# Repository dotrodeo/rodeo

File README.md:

# Rodeo

A modular **synthesizer hardware ecosystem**: one host *motherboard*, a family of
control-surface *daughterboards*, and *instrument instances* built by combining them.
This repository is the single home for all of it — board designs (KiCad), firmware,
and the design docs that tie them together.

## Layout

The current hardware is **Rev B**, in [`hardware/`](hardware/). Rev A, the prototype
generation that rodeo-001 and rodeo-002 were built on, is kept whole in
[`rev-a/`](rev-a/); the tree as it stood before this split is tagged `rev-a-final`.

| Directory | What it is |
|---|---|
| [`hardware/`](hardware/) | **Rev B, the boards in production.** One self-contained KiCad project per board, each with its README and JLC fab outputs. |
| [`hardware/rodeo-motherboard/`](hardware/rodeo-motherboard/) | The host board, a Daisy Seed carrier: two codecs (8 audio channels), 10 general-purpose I/O, MIDI, I²C taps, internal SD, and the satellite chain on USART3. Every decision and its reasoning: [`docs/rev-b.md`](hardware/rodeo-motherboard/docs/rev-b.md). |
| [`hardware/rodeo-pot-bank-4/`](hardware/rodeo-pot-bank-4/), [`hardware/rodeo-encoder-bank-4/`](hardware/rodeo-encoder-bank-4/) | Satellites: four pots or four encoders with switches, each read by a CH32V003 on the chain. |
| [`hardware/rodeo-power-usbc/`](hardware/rodeo-power-usbc/), [`hardware/rodeo-power-barrel/`](hardware/rodeo-power-barrel/) | Power input boards: USB-C (power and USB data), or USB-C plus a barrel jack and an LED-strip rail. |
| [`hardware/rodeo-power-switch/`](hardware/rodeo-power-switch/) | The power switch: a latching push button on the back panel (with a printed cap), cabled to the motherboard's J3. |
| [`hardware/rodeo-audio-3.5mm/`](hardware/rodeo-audio-3.5mm/), [`hardware/rodeo-midi/`](hardware/rodeo-midi/) | Rear-panel jack boards: four stereo 3.5 mm audio jacks, and TRS MIDI in and out. |
| [`hardware/panels/`](hardware/panels/) | The back panels: one FR4 panel per rear board, generated from the cut-out table and screwed to the rails. |
| [`hardware/mounting/`](hardware/mounting/) | The printed rear rail, top rail and motherboard frame, and the grid every board's holes sit on. |
| [`hardware/docs/`](hardware/docs/) | Cross-board docs, such as the [silkscreen checklist](hardware/docs/silkscreen.md). |
| [`rodeo-sdk/`](rodeo-sdk/) | **The code everything is built on**: driver libraries, the pure host-tested logic, bring-up examples, a copy-to-start template, host tools, and the vendored libDaisy/DaisySP. An instrument points `RODEO_ROOT` here and consumes it; it does not copy it. It is being rewritten for Rev B ([plan](planning/REV_B_PLAN.md)); the Rev A instruments build against the frozen Rev A SDK in `rev-a/rodeo-sdk/`. |
| [`instruments/`](instruments/) | **Reference instruments** built from the boards. [`rodeo-001`](instruments/rodeo-001/) is the first ([control map](instruments/rodeo-001/docs/RODEO_CONTROL_MAP.md), [enclosure spec](instruments/rodeo-001/docs/RODEO_ENCLOSURE_SPEC.md)); [`rodeo-002`](instruments/rodeo-002/) is a multi-engine digital polysynth into a texture chain ending in a granular delay ([concept](instruments/rodeo-002/docs/RODEO_002_CONCEPT.md), [firmware](instruments/rodeo-002/firmware/), tagged `rodeo-002/v5.0.0`). Both run on Rev A. |
| [`rev-a/`](rev-a/) | **The Rev A prototypes**: the [motherboard](rev-a/rodeo-motherboard/) (2× ADS114S08, 24 analog channels), the [encoder hub](rev-a/rodeo-encoder-hub/) and its firmware, the encoder, button, potentiometer and rotary-switch daughterboards, the panelisation templates, and [the SDK as it was for Rev A](rev-a/rodeo-sdk/) (frozen at `rodeo-sdk/v0.2.0`, with its own libDaisy/DaisySP). Superseded, but still what the two instruments run on. |
| [`tools/`](tools/) | Host tools, including the KiCad review and JLC fab-output scripts in [`tools/kicad/`](tools/kicad/). |
| [`web/`](web/) | **The website**: an Astro site and the build log, plus the docs that govern it: [brand](planning/WEB_BRAND.md), [architecture](planning/WEB_ARCHITECTURE.md), [claims audit](planning/WEB_CLAIMS_AUDIT.md). |

> **Naming, so nobody trips on it again:** `rodeo-motherboard` is the *host board*;
> `rodeo-001` is the *first instrument built from the ecosystem*. They are different
> things.
>
> **The SDK is not the motherboard's firmware.** It serves every instrument, so it is
> its own thing at the top level, and anything in it that names a specific knob or a
> specific sound is in the wrong place. (`rev-a/rodeo-encoder-hub/firmware/` is
> different again: that really is one board's own firmware, for the STM32C0 on the hub.)

## Where the source-of-truth docs live

- **Rev B motherboard** → [`hardware/rodeo-motherboard/docs/rev-b.md`](hardware/rodeo-motherboard/docs/rev-b.md), and the satellite wire protocol in [`RODEO_SATELLITE_CHAIN_CONTRACT.md`](hardware/rodeo-motherboard/docs/RODEO_SATELLITE_CHAIN_CONTRACT.md).
- **Rev A motherboard pin map / topology** → `rev-a/rodeo-sdk/common/board.h` (generic board facts only) and [`rev-a/rodeo-motherboard/docs/hardware-map.md`](rev-a/rodeo-motherboard/docs/hardware-map.md) (verified against the PCB).
- **Encoder-hub ↔ motherboard I²C register contract** (Rev A) → [`rev-a/rodeo-motherboard/docs/RODEO_HUB_I2C_CONTRACT.md`](rev-a/rodeo-motherboard/docs/RODEO_HUB_I2C_CONTRACT.md).
- **ADC driver-library design** → [`planning/RODEO_ADC_LIB_DESIGN.md`](planning/RODEO_ADC_LIB_DESIGN.md).
- **rodeo-001 control map** (which physical control does what) → [`instruments/rodeo-001/docs/RODEO_CONTROL_MAP.md`](instruments/rodeo-001/docs/RODEO_CONTROL_MAP.md). This is the instance contract shared by firmware, hardware, and the panel layout.
- **rodeo-001 enclosure / panel** → [`instruments/rodeo-001/docs/RODEO_ENCLOSURE_SPEC.md`](instruments/rodeo-001/docs/RODEO_ENCLOSURE_SPEC.md).
- **rodeo-002 concept + control map** → [`instruments/rodeo-002/docs/`](instruments/rodeo-002/docs/): the voice and engine budget measured on hardware, and the locked panel/channel map.

## Building the firmware

See [`rodeo-sdk/README.md`](rodeo-sdk/README.md) for
the toolchain, `make deps`, and the numbered bring-up examples (blink → audio → MIDI →
ADC → poly synth → encoder scan → OLED).

## Repo notes

- One git repo; `libDaisy` and `DaisySP` are submodules (`git submodule update --init --recursive`).
- Every board is a self-contained KiCad project. A Rev B board keeps its own symbols, footprints and 3D models in its `lib/`; everything else comes from KiCad's standard libraries. Nothing points outside the board's folder, so a folder can be moved or copied on its own.

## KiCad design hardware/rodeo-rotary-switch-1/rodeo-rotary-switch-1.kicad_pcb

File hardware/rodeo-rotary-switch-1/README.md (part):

# Rodeo satellite: rotary switch ×1

One 4-position rotary selector switch with a status LED, read by a CH32V003 on the
satellite chain: board kind 4, the contract's single `SWITCH` slot. For a mode or
range selector whose position must be absolute and survive a power cycle, which an
encoder's can't. It's built like the [single pot](../rodeo-pot-1/README.md): the same
mounting, MCU, connectors and pin map, with the switch read on the pot's ADC pin
through a resistor ladder that has room for 8 positions. The switch's footprint is
bigger than the pot's, so the board is 25 × 37.5 mm, half a grid slot taller: two
of them fill three 25 mm slots (see [Board](#board)). Wire contract:
[`RODEO_SATELLITE_CHAIN_CONTRACT.md`](../rodeo-motherboard/docs/RODEO_SATELLITE_CHAIN_CONTRACT.md).

Specified 2026-10-26. Schematic and layout: a first pass by Claude, 2026-10-26, from
Derek's single pot files (see [Layout](#layout)). For Derek's review.

## Decisions

* **Alps SRBV141404, 4 positions** (see [Switch](#switch-sw1-alps-srbv141404-c209777)).
  It's the one rotary switch JLC stocks in quantity that has a bushing to hang the
  board from and end stops. Its M9 bushing is the single pot's, so the panel hole and
  nut are the same.
* **One ADC pin, not one GPIO per position.** The switch's positions tap a resistor
  ladder, and its common goes to the single pot's wiper pin (PA2). The board is then
  the single pot with a different part on top.
* **The ladder has 8 taps though the switch has 4.** A switch with fewer positions
  just never reaches the upper taps, so the same ladder and the same kind-4 decoder
  would serve an 8-position switch (the SRBV181004, wired the same) with no
  firmware change. The four extra 0603 resistors cost almost nothing.
* **Taps at 1/9 to 8/9 of 3V3, never at the rails.** Nine equal resistors make eight
  taps 114 counts apart. A 1 MΩ pull-down on the common means a reading near 0 V is
  "between positions", never position 1. The ladder runs from the same 3V3 as the
  ADC's reference, so the reading is ratiometric: a sagging supply at the end of a
  long chain doesn't move it.
* **The common's 100 nF holds the last position through the switch's gap.** The
  SRBV's contacts are non-shorting, so the common is open for a moment at each step.
  Through 1 MΩ the cap's voltage barely moves in that time (τ = 0.1 s), so the
  reading goes from one tap straight to the next. Firmware also waits for a stable
  reading before reporting a new position.
* **Same MCU, CH32V003F4P6, and the single pot's pin map** (`PRESENT` PC3, LED PC6, ID
  on PD3 fed from PC2), for the reasons in its spec.
* **Hung on the switch's M9 bushing and nut, plus an M2 standoff at H1,** as the
  single pot is. The standoff stops the board turning when the knob is forced
  against an end stop.

## Switch SW1: Alps SRBV141404 (C209777)

1 pole, 4 positions, 30° steps with end stops, non-shorting. M9 threaded bushing,
7 mm long; Ø6 mm shaft with a 4.5 mm flat, 15 mm from the mounting face to the tip
(Derek, from Alps' drawing). Body 16.2 × 18.5 × 7.5 mm. Turning torque 30 ± 15 mN·m,
lighter than a pot's drag, so it will feel light. Rated 0.3 A at 16 V; life 10,000
steps. 434 in stock at JLC on 2026-10-26, so it is assembled with the board, like
the pots.

* **The 8-position sibling, SRBV181004 (C390927),** has the same body and footprint,
  and the board wires all eight positions, so it takes either as a BOM choice. Only 40 in stock at JLC
  on 2026-10-26.
* **Footprint and 3D model: in `lib/`,** from EasyEDA (C209777) through
  easyeda2kicad. `rodeo_rotary_switch:SW_Alps_SRBV` has 10 terminals in two rows of
  five, 2.54 mm pitch, the rows 18.3 mm apart (y = ±9.15 from the shaft), and two
  Ø2 mm mounting lugs 16 mm apart (x = ±8, y = −1.1). EasyEDA's SRBV181004 footprint
  is identical, so the 4- and 8-position parts are a BOM swap. Alps' own STEP model
  (made in Creo) sits on it correctly: terminals in their holes, lugs in theirs.
* **Symbol: `lib/rodeo_rotary_switch.kicad_sym`,** EasyEDA's, with its footprint and
  LCSC fields set, and its pins named from Alps' standard circuit diagram (1 pole):
  * **Terminals 1 and 10 are the common, `C`,** one in each row. Wire both to
    `SW_POS`.
  * **Terminals 2–9 are positions `P1`–`P8`,** in that order around the rotor. On the
    SRBV141404, 6–9 are dummy terminals with no contact behind them; positions 1–4
    are terminals 2–5.
  * **Pads 11 and 12 are the lugs, `MP`:** tie them to `GND`.
  * The diagram's terminal layout (6–10 along the top, 5–1 along the bottom, left to
    right) matches the footprint seen from the top, which faces the panel, so it's
    drawn from the knob side. Read that way, 2 → 5 runs clockwise, so position 1 is
    the counter-clockwise end. Check the direction at bring-up.
* **Considered and set aside:** the Alps SRRM1C6200 (C278333), JLC's only
  12-position switch: 24.9 × 31 mm, too big for the board, it turns endlessly,
  shorting contacts, and Alps lists it as not recommended for new designs. The
  Taiwan Alpha SR1712F would allow up to 8 positions with an M9 bushing, but JLC
  doesn't stock it.

## Board

* **Outline 25 × 37.5 mm, 2 mm corners.** 25 mm wide like the other single boards,
  and 1.5 grid slots tall, so two rotary switches stack into three 25 mm slots.
  Coordinates are from the board's top-left corner as seen from the front (panel
  side), y down; the LED end is the top, as on the single pot.
  * **Switch SW1 at the board's centre, (12.5, 18.75), in the footprint's own
    orientation:** terminal rows across the board at y = 9.6 and 27.9 (x = 7.4–17.6),
    lugs at (4.5, 17.65) and (20.5, 17.65). Alps' model puts the shaft on the
    footprint's origin. Two boards stacked in 75 mm put their shafts 37.5 mm apart,
    symmetric in the three slots. Panel hole Ø9.5 mm for the M9 bushing, as for the
    pots.
  * **LED D1 at (12.5, 3.0) with R1 beside it, H1 at (22.5, 2.5) and J3 at x = 23,
    y = 6–13.6:** the single pot's positions.
  * **Chain connectors J1 (IN) at (3, 32.5) and J2 (OUT) at (22, 32.5):** 5 mm above
    the bottom edge, as on the single pot, either side of the bottom terminal row.
  * **U1 at the centre of the back, (12.5, 18.75),** between the terminal rows, under
    the switch body. C2 and C3 (VDD) to its left, C1 and R15 (`SW_POS`) to its right.
  * **The ladder along the terminal rows:** R6–R9 in two staggered rows under
    terminals 6–10, R11–R14 above terminals 1–5, each between the two terminals it
    joins (the ends, R6 from `+3V3` and R14 to `GND`, beside terminals 9 and 2), and
    R10 (T5–T4) at the left edge, joining the two rows.
  * **The ID divider R3, R5** top left (front view), above the left lug; **R2, R4**
    (33 Ω) on the right, above J2.
* **The LED is 15.75 mm from the shaft,** so a knob up to about Ø27 mm clears its
  hole (the single pot's limit is Ø14.8 mm).
* **Top side (faces the panel): the switch only**, through-hole. **Bottom: every SMD
  part**, the ladder included, so JLC's SMT is single-sided.
* **Knobs level with the pots' for free.** Both hang from the panel's underside by
  the mounting face, and both shafts rise 15 mm from it, so a rotary switch's knob
  sits at the pots' height. The shaft is Ø6 mm with a 4.5 mm flat, like the pots',
  so the same knobs should fit; check one on the first boards.
* **Standoff about 7.5 mm, not the single pot's 10 mm:** the mounting face is the top
  of the 7.5 mm body, sitting on the board. M2 standoffs are commonly 6 or 8 mm, so
  measure the seated height on the first board and pick the length (or a washer)
  from that.
* **The 7 mm bushing** takes the panel and the nut with room to spare.
* **2 layers,** as on the single pot.
* **Silkscreen.** Back: `RODEO / ROTARY / SWITCH` top right (seen from the back),
  `Kind 4 / Rev B1 / 2026-10` between the connectors, `CHAIN IN` / `CHAIN OUT` with
  pin-1 marks, `S V G N` at J3, and position numbers `1`–`4` under terminals 2–5.
  Front: the licence, source and `© 2026 DOT RODEO LLC` below the switch, hidden
  by the panel once fitted (there's no room left on the back).

## The ladder

```
+3V3 ─ R ─ T8 ─ R ─ T7 ─ R ─ T6 ─ … ─ T2 ─ R ─ T1 ─ R ─ GND      (9 × R)

Tn ── terminal n+1 (position n)  common (terminals 1, 10) ── SW_POS ── PA2
                                 SW_POS: 1 MΩ to GND, 100 nF to GND
```

* **R = 4.7 kΩ (1 %), nine of them:** 42.3 kΩ in all, 78 µA. Tap n sits at
  n/9 × 3V3: 114, 227, 341, 455, 568, 682, 796 and 909 counts for positions 1–8.
* **Tap n goes to terminal n + 1,** all eight. The SRBV141404 uses taps 1–4 on
  terminals 2–5; taps 5–8 land on its dummy terminals 6–9, which connect to nothing
  inside, so the same board takes the 8-position SRBV181004 as a BOM swap.
* The worst-case source impedance at a tap is under 11 kΩ. The 1 MΩ load pulls a tap
  down by about 1 % at most, 6 counts, against 57 counts to the next decision
  point.
* **Decoding:** position = round(9 × reading / 1023), valid when it's 1–8 and the
  reading is within 0.3 of a step of the tap (the ID resistor's rule). A reading
  near 0 V, or between taps, keeps the last position. A new position is reported
  after it has read the same for 10 ms.
* **`SWITCH` slot:** `D0` = position − 1, so 0–3 here (0–7 with an 8-position
  switch), as the contract's position index. Until the first valid reading after
  power-up, the slot is `EMPTY`.

## Layout

`rodeo-rotary-switch-1.kicad_sch` and `.kicad_pcb` start from the single pot's,
changed by script rather than by hand:

* **Schematic:** RV1 out, SW1 (`rodeo_rotary_switch:SRBV141404`) in, with terminal 1
  on the old wiper net (renamed `POT_1` → `SW_POS`) and terminal 10 on a `SW_POS`
  label; the lugs to `GND`. The ladder R6–R14 is a column of nine 4.7 kΩ with labels
  `T1`–`T8` at its joints and on terminals 2–9; R15 1 MΩ from `SW_POS` to `GND`; R5
  715 Ω → 3.65 kΩ. ERC: no errors or warnings.
* **PCB:** the outline, zones and panel guides stretched to 25 × 37.5 mm; RV1 out;
  SW1, R6–R15 in; every part but D1, R1, J3 and H1 placed afresh (above). The single
  pot's tracks didn't survive the move, so the whole board was routed by a grid
  router: 0.1 mm grid, 45° steps with a cost per turn, 0.2 mm signal tracks, 0.3 mm
  `+3V3` and `GND`, 0.2 mm clearance, 0.6/0.3 mm vias; signals on B.Cu where they can,
  `GND` on F.Cu under its pour, U1's decoupling routed first.
* **DRC, with schematic parity:** two edge-clearance errors, both D1's own pads at its
  lens hole, as on the single pot; no unconnected items, no footprint or parity
  errors.
* **Worth a look in KiCad:**
  * The routing is correct, not pretty: 38 vias (11 of them `GND` to the front
    pour), and some runs go the long way round. Re-route as you see fit.
  * `+3V3` runs partly on F.Cu, cutting the front `GND` pour, and so does `SW_POS`.
  * F.Cu tracks pass under the switch body, under solder mask. Check Alps' drawing for
    anything metal on the body's underside.
  * J1 pin 2 and R6 pin 1 connect solidly to the `+3V3` pour (a local override): with
    the tracks beside them, a thermal relief got only one spoke.
  * References R2, R5, R9, R12, R14, R15 and C1 are on B.Fab; there was no room on
    the back silk clear of pads.

## MCU: CH32V003F4P6 (C5187096), TSSOP-20

The single pot's map, with `SW_POS` where its wiper goes.

| Pin | Name | Connection |
|---|---|---|
| 9 | VDD | `+3V3`; 1 µF and 100 nF to `GND` at the pin |
| 7 | VSS | `GND` |
| 3 | PD6 | `SAT_RX`: J1 IN pin 3 |
| 11 | PC1 | `SAT_RX` (same net) |
| 2 | PD5 | 33 Ω → J2 OUT pin 3 (`DATA_FWD` out) |
| 10 | PC0 | 33 Ω → `DATA_RET` |
| 13 | PC3 | `PRESENT`: J2 OUT pin 5 (internal pull-up) |
| 12 | PC2 | `ID_DRV`: the ID divider's top, driven high only while reading the ID |
| 20 | PD3 (A4) | `ID`: 10 kΩ from PC2, 3.65 kΩ (R_ID, kind 4) to `GND` |
| 6 | PA2 (A0) | `SW_POS`: the switch common (ladder above) |
| 16 | PC6 | 1.5 kΩ → D1 anode; cathode to `GND` |
| 18 | PD1 | `SWIO`: programming pad |
| 4 | PD7 | `NRST`: programming pad |
| others | | no connect |

## Connectors J1 (IN), J2 (OUT): JST SH 5-pin vertical, BM05B-SRSS-TB (C160391)

The satellites' pinout:

1. `GND`
2. `+3V3`, straight through
3. `DATA_FWD`: `SAT_RX` on J1; on J2, the 33 Ω from PD5
4. `DATA_RET`: straight through, tapped by the 33 Ω from PC0
5. `PRESENT`: `GND` on J1, PC3 on J2

Mounting pads unconnected.

## Board-kind ID

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
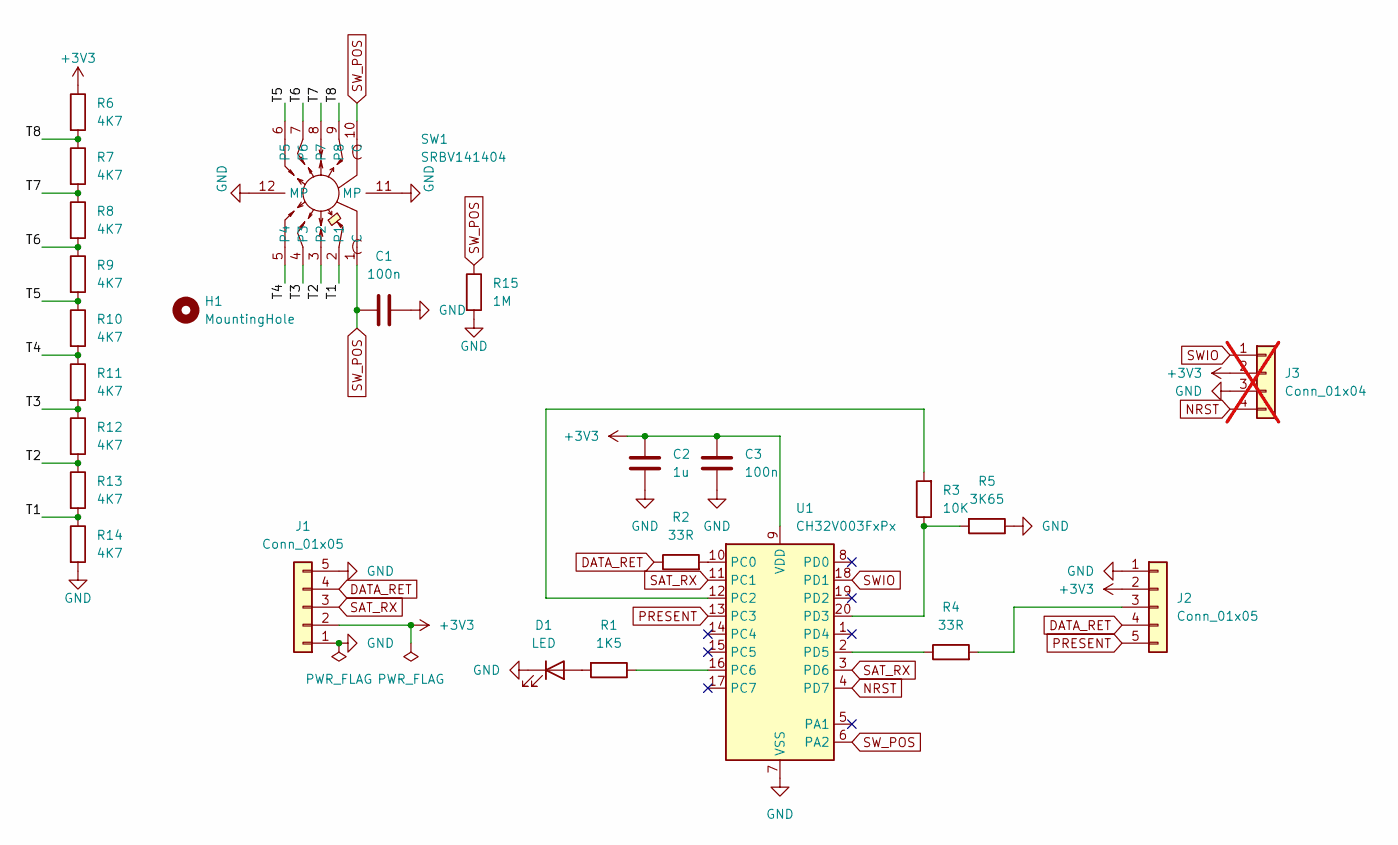
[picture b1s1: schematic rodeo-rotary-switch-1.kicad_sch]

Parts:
C1, C3: 100n; C_0402_1005Metric; LCSC Part C1525
C2: 1u; C_0402_1005Metric; LCSC Part C52923
D1: LED; LED_1206_3216Metric_ReverseMount_Hole1.8x2.4mm; LCSC Part C125107
H1: MountingHole; MountingHole_2.2mm_M2
J1, J2: Conn_01x05; JST_SH_BM05B-SRSS-TB_1x05-1MP_P1.00mm_Vertical; LCSC Part C160391
J3: Conn_01x04; PinHeader_1x04_P2.54mm_Vertical; not fitted
R1: 1K5; R_0603_1608Metric; LCSC Part C22843
R2, R4: 33R; R_0603_1608Metric; LCSC Part C23140
R3: 10K; R_0603_1608Metric; LCSC Part C25804
R5: 3K65; R_0603_1608Metric; LCSC Part C2930089
R6, R7, R8, R9, R10, R11, R12, R13, R14: 4K7; R_0603_1608Metric; LCSC Part C23162
R15: 1M; R_0603_1608Metric; LCSC Part C22935
SW1: SRBV141404; SW_Alps_SRBV; MPN SRBV141404; LCSC Part C209777
U1: CH32V003FxPx; TSSOP-20_4.4x6.5mm_P0.65mm; LCSC Part C5187096

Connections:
+3V3: C2.2, C3.2, J1.2, J2.2, J3.2, R6.1, U1.9 (VDD)
/T1: R13.2, R14.1, SW1.2 (P1)
/T2: R12.2, R13.1, SW1.3 (P2)
/T3: R11.2, R12.1, SW1.4 (P3)
/T4: R10.2, R11.1, SW1.5 (P4)
/T5: R9.2, R10.1, SW1.6 (P5)
/T6: R8.2, R9.1, SW1.7 (P6)
/T7: R7.2, R8.1, SW1.8 (P7)
/T8: R6.2, R7.1, SW1.9 (P8)
DATA_RET: J1.4, J2.4, R2.1
GND: C1.2, C2.1, C3.1, D1.1 (K), J1.1, J1.5, J2.1, J3.3, R5.1, R14.2, R15.2, SW1.11 (MP), SW1.12 (MP), U1.7 (VSS)
NRST: J3.4, U1.4 (PD7)
unnamed: D1.2 (A), R1.2
unnamed: J2.3, R4.2
unnamed: R2.2, U1.10 (PC0)
unnamed: R3.2, U1.12 (PC2)
unnamed: R1.1, U1.16 (PC6)
unnamed: R3.1, R5.2, U1.20 (PD3)
unnamed: R4.1, U1.2 (PD5)
PRESENT: J2.5, U1.13 (PC3)
SAT_RX: J1.3, U1.3 (PD6), U1.11 (PC1)
SWIO: J3.1, U1.18 (PD1)
SW_POS: C1.1, R15.1, SW1.1 (C), SW1.10 (C), U1.6 (PA2)

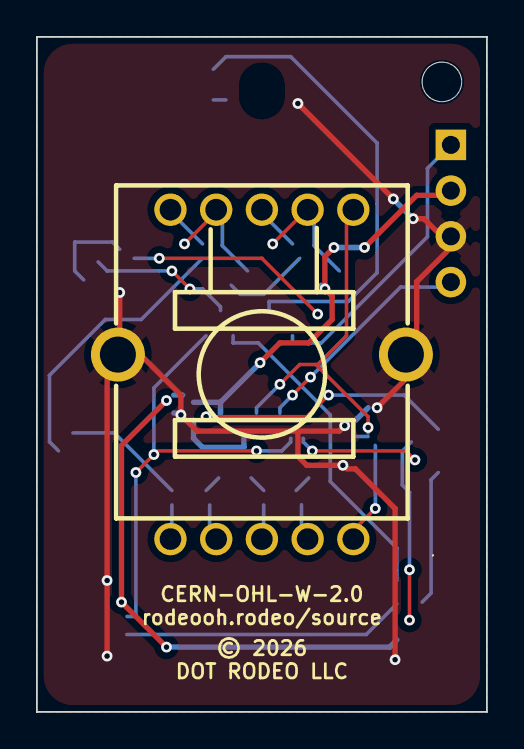
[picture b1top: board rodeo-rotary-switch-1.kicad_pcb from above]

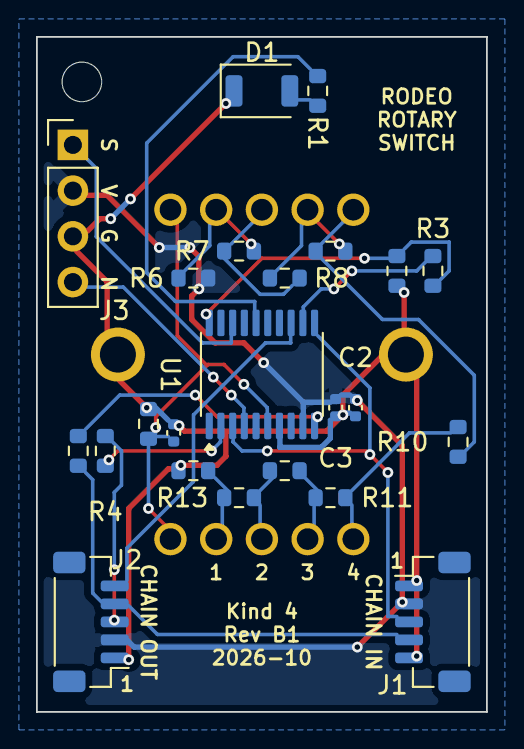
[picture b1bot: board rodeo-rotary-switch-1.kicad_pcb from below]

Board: 2 copper layers, 25.0 x 37.5 mm, 25 parts (23 on the bottom side), 23 nets.

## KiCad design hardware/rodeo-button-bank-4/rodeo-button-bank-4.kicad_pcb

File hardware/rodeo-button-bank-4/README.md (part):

# Rodeo satellite: button bank ×4

Four momentary buttons in a row on 12.5 mm centres, each with an addressable RGB LED
beside it, read and driven by one CH32V003 on the satellite chain. The third Rev B
satellite, after the [pot bank](../rodeo-pot-bank-4/README.md) and the
[encoder bank](../rodeo-encoder-bank-4/README.md). Wire contract:
[`RODEO_SATELLITE_CHAIN_CONTRACT.md`](../rodeo-motherboard/docs/RODEO_SATELLITE_CHAIN_CONTRACT.md).

Specified 2026-10-19; schematic drawn 2026-10-19; laid out by Derek and routed 2026-10-22.

## Decisions

* **The buttons aren't lit; an LED sits beside each one.** RGB-illuminated tact
  switches at this size are either out of stock at JLC (E-Switch TL3220, $8 each)
  or thinly documented (HOOYA TC-1196A-RGB). No switch under ~14 mm passes light
  through for a reverse-mount LED. A plain switch plus a separate LED keeps both
  parts cheap and well stocked.
* **WS2812B-2020-V6 LEDs, not RGBW.** The in-stock RGBW parts (SK6812 family) need
  3.7–5.5 V and 0.65 × VDD on their data input, so they'd need the aux 5 V and a level
  shifter. The WS2812B-2020-V6 runs from 3.3–5.3 V and switches at 0.55 × VDD, so a
  3.3 V MCU drives it at either supply.
* **The LEDs run from the chain's 3V3 or from an optional aux 5 V,** switched
  automatically (see [LED supply](#led-supply)). Without the aux cable the buttons
  and LEDs both work, with the LEDs capped in firmware to fit the chain's budget
  and dimmer on blue and green at the end of a long chain. With it, full brightness.

## Board

Built like the [pot bank](../rodeo-pot-bank-4/README.md) and the
[encoder bank](../rodeo-encoder-bank-4/README.md): a 20 mm strip with the controls on
the panel side.

* **Outline 20 × 75 mm, rounded corners.** Coordinates are from the board's top-left
  corner, y down the strip; the MCU end is the top.
  * Switch centres at x = 10 mm, y = 18.75, 31.25, 43.75, 56.25 mm (12.5 mm apart).
  * LED centres at x = 17 mm, level with each switch: 7 mm to its right.
  * M2 mounting holes (`MountingHole_2.2mm_M2`) at (10, 3) and (10, 72).
* **Top side (faces the panel): the four switches and four LEDs,** plus the LEDs'
  decoupling caps and the LED supply parts (Q1, D5, C7, C8) by the aux connectors.
* **Bottom side:** the MCU and its passives, the chain connectors J1 (IN, y = 25) and
  J2 (OUT, y = 50) between the switch pins, the aux connectors J3/J4 at the bottom
  end, and the unfitted programming header J5. **Assembled on both sides**, since
  the LEDs must face the panel.
* **4 layers:** signals on F.Cu and B.Cu; In1 solid `GND`; In2 split, `+3V3` (which
  carries the chain's pass-through from J1 to J2) on the left and `V_LED` along the
  right edge under the LEDs, with `AUX_5V` routed in the gap.
* **The board hangs from the top panel on two M2 standoffs.** Buttons have no
  bushing to hang from, and pressing them pushes the board away from the panel, so
  the standoffs carry the load. Standoff length, switch height and caps are chosen
  together with the panel (see [Open](#open)).
* **Silkscreen:** button numbers `1`–`4` beside the switches and the `RODEO`
  wordmark on the front. On the back: `RODEO BUTTON BANK ×4`,
  `Kind 7 · Rev B1 · 2026-10`, the licence and source, `© 2026 DOT RODEO LLC`,
  `CHAIN IN` / `CHAIN OUT`, `AUX 5V` and `+` at J3 and J4 (they're in parallel, so
  either can be the input), and `S V G N` at J5.

## Switches SW1–SW4: Omron B3F-1052 (C87037)

6 × 6 mm through-hole tact switch, 7.3 mm to the top of a square stem that takes
Omron's B32 snap-on caps, 1.5 N, rated 300,000 operations. 5,052 in stock at JLC on
2026-10-19.

* **Footprint: the common 6 × 6 mm through-hole pattern, pins 6.5 × 4.5 mm.**
  Omron B3F, Alps SKHH and C&K PTS645 all fit it, so the switch height is a BOM
  choice: e.g. Alps SKHHAPA010 (C139809) has a 9.5 mm round stem for a stem
  through the panel without a cap.
* Each switch: one side to `GND`, the other to its MCU pin with the internal
  pull-up on. Firmware debounces. Switch n is button n, numbered from the IN end.

## LEDs D1–D4: Worldsemi WS2812B-2020-V6 (C52917434)

2.0 × 2.0 × 0.84 mm, 24-bit GRB, 800 kbit/s, 12 mA per colour (36 mA per LED at full
white). Supply 3.3–5.3 V; data input high at 0.55 × VDD. 860,680 in stock at JLC on
2026-10-19.

* Chained D1 → D2 → D3 → D4, D1 beside SW1. `LED_DIN` from PC6 through R5 100 Ω.
* 100 nF from `V_LED` to `GND` at each LED (C3–C6), as the datasheet's application
  circuit shows.
* **Light pipes.** Each LED is meant to sit under a 3 mm light pipe pressed into the
  panel (Bivar PLP1 from behind, PLPC3 from the front, or a printed clear rod), or
  to show through a bare Ø3.2 mm panel hole. On the board:
  * nothing taller than the LED within 2.5 mm of an LED centre, so a pipe can sit
    within ≈0.5 mm of it (the 0402 decoupling caps at 2.5 mm are lower than the LED);
  * LED centres exactly as listed above, for the panel drawing;
  * one tented `GND` via per LED sits 1.84 mm from its centre: flat under a pipe,
    visible through a bare hole.
  The pipe length follows from the standoff length (the LED's top is 0.84 mm above
  the board).
* **Button caps can be up to ≈9.8 mm square:** that leaves a 0.5 mm web of panel
  between a cap's hole and the Ø3.2 mm LED hole 7 mm away.

## LED supply

`V_LED` feeds the four LEDs and nothing else.

```
AUX_5V (J3 pin 1) ── D5 B5819W ──┬── V_LED ── D1…D4
                                 │
+3V3 ── Q1 AO3401A (drain→source)┘    gate ← AUX_5V
```

* **Aux present:** D5 feeds `V_LED` at ≈4.7 V. Q1's gate is at 5 V and its source
  at 4.7 V, so it's off, and its body diode (drain at 3.3 V) is reverse biased: the
  chain's 3V3 sees no LED current.
* **Aux absent:** R6 + R7 (below) pull Q1's gate to `GND`, so Q1 turns on (V_GS ≈ −3 V,
  85 mΩ) and the chain's 3V3 feeds `V_LED`. D5 keeps `V_LED` off the aux pins.
* **Q1: AO3401A (C15127)**, P-channel, SOT-23, JLC basic part. **D5: B5819W
  (C8598)**, 1 A Schottky, SOD-123, basic part.
* 10 µF on `V_LED` (C7) and 10 µF at J3 (C8).
* **`AUX_SENSE`:** R6 100 kΩ / R7 100 kΩ from `AUX_5V` to `GND`, midpoint to PC4
  (A2), so firmware knows which supply the LEDs are on and sets the brightness cap.
  2.5 V with aux, 0 V without; 25 µA. The same divider is Q1's gate pull-down, so
  Q1 needs no resistor of its own.
* **Data level:** with aux, the LEDs need 0.55 × 4.7 ≈ 2.6 V on `LED_DIN`; the MCU's
  output high is its own supply, ≥ 2.9 V even at the end of a 30-satellite chain.

## Aux connectors J3 (IN), J4 (OUT): JST PH 2-pin vertical SMD, B2B-PH-SM4-TB (C160352)

| Pin | Signal |
|---|---|
| 1 | `AUX_5V` |
| 2 | `GND` |

`AUX_5V` passes straight from J3 to J4, so one aux feed can serve several LED
satellites in a row. Both on the bottom side. The pin order matches the 5 V aux
output planned for the motherboard's next revision
([`revisions.md`](../docs/revisions.md)). `AUX_5V` runs on 0.4–0.8 mm tracks (up to 144 mA).

## MCU: CH32V003F4P6 (C5187096), TSSOP-20

Ring closing and connectors as on the pot bank (USART1 mapping 0 normally, mapping
3 when last; IN `DATA_FWD` on both PD6 and PC1).

| Pin | Name | Connection |
|---|---|---|
| 9 | VDD | `+3V3`; C2 100 nF and C1 1 µF to `GND` at the pin |
| 7 | VSS | `GND` |
| 3 | PD6 | `SAT_RX`: J1 IN pin 3 |
| 11 | PC1 | `SAT_RX` (same net) |
| 2 | PD5 | R2 33 Ω → J2 OUT pin 3 |
| 10 | PC0 | R1 33 Ω → `DATA_RET` |
| 13 | PC3 | `PRESENT`: J2 OUT pin 5 (internal pull-up) |
| 20 | PD3 (A4) | `ID`: R3 10 kΩ from `+3V3`, R4 8.66 kΩ (R_ID, kind 7) to `GND` |
| 16 | PC6 | `LED_DIN` via R5 100 Ω: SPI1 MOSI, which clocks the WS2812 bit stream |
| 14 | PC4 (A2) | `AUX_SENSE` |
| 5 | PA1 | `SW_1` |
| 6 | PA2 | `SW_2` |
| 1 | PD4 | `SW_3` |
| 8 | PD0 | `SW_4` |
| 18 | PD1 | `SWIO`: programming pad |
| 4 | PD7 | `NRST`: programming pad |
| 12, 15, 17, 19 | PC2, PC5, PC7, PD2 | no connect (spare) |

* **The switches use different pin numbers (1, 2, 4, 0)**, so each could have its own
  EXTI line if firmware ever wants interrupts instead of polling.
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
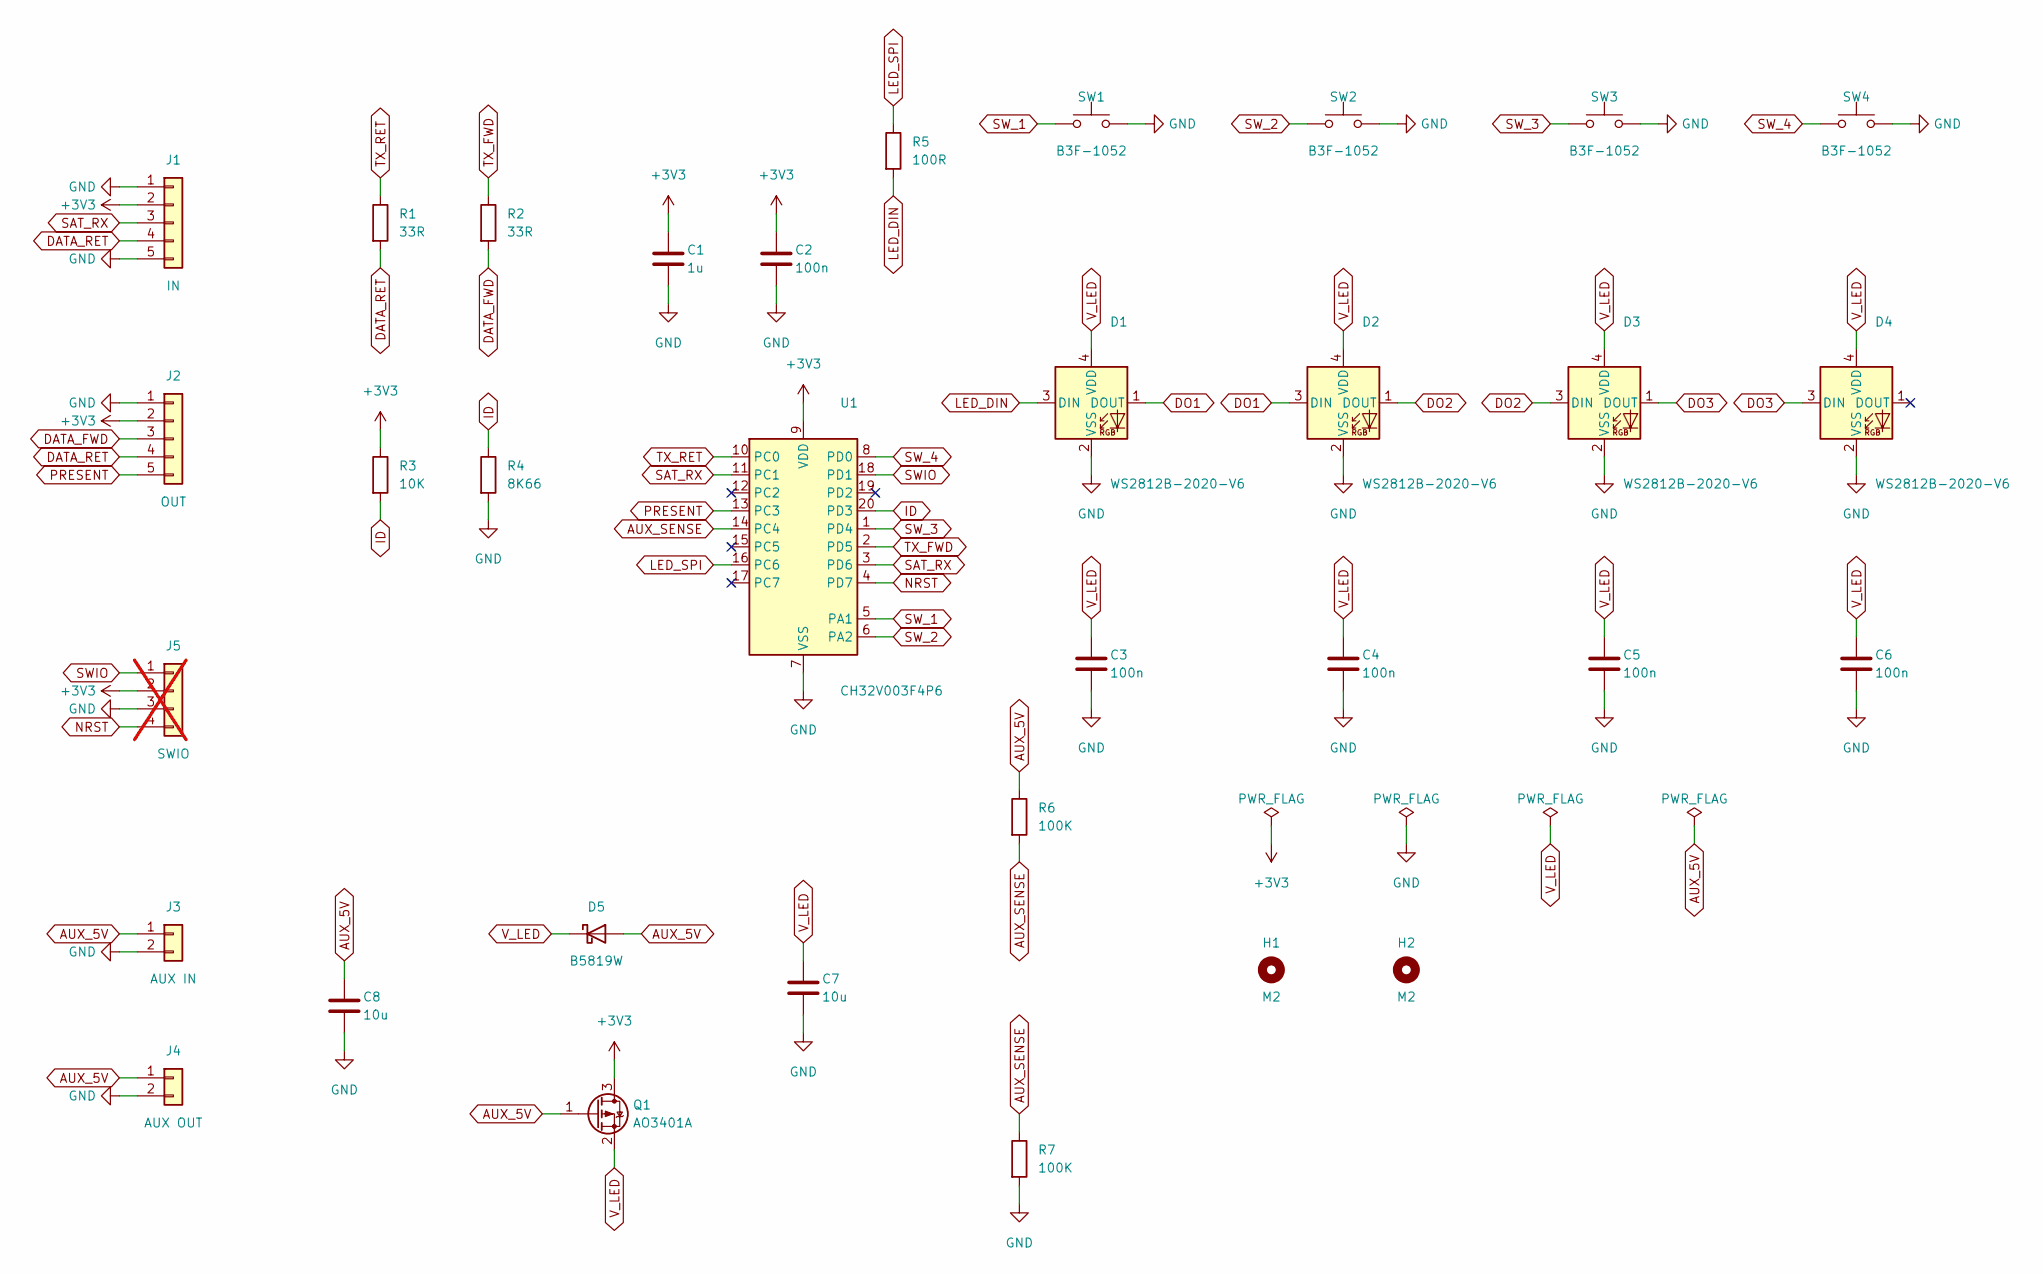
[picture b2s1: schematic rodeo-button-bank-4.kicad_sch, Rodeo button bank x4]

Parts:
C1: 1u; C_0402_1005Metric; LCSC Part C52923
C2, C3, C4, C5, C6: 100n; C_0402_1005Metric; LCSC Part C1525
C7, C8: 10u; C_0603_1608Metric; LCSC Part C19702
D1, D2, D3, D4: WS2812B-2020-V6; LED_WS2812B-2020_PLCC4_2.0x2.0mm; LCSC Part C52917434
D5: B5819W; D_SOD-123; LCSC Part C8598
H1, H2: M2; MountingHole_2.2mm_M2
J1: IN; JST_SH_BM05B-SRSS-TB_1x05-1MP_P1.00mm_Vertical; LCSC Part C160391
J2: OUT; JST_SH_BM05B-SRSS-TB_1x05-1MP_P1.00mm_Vertical; LCSC Part C160391
J3: AUX IN; JST_PH_B2B-PH-SM4-TB_1x02-1MP_P2.00mm_Vertical; LCSC Part C160352
J4: AUX OUT; JST_PH_B2B-PH-SM4-TB_1x02-1MP_P2.00mm_Vertical; LCSC Part C160352
J5: SWIO; PinHeader_1x04_P2.54mm_Vertical; not fitted
Q1: AO3401A; SOT-23; LCSC Part C15127
R1, R2: 33R; R_0603_1608Metric; LCSC Part C23140
R3: 10K; R_0603_1608Metric; LCSC Part C25804
R4: 8K66; R_0603_1608Metric; LCSC Part C23114
R5: 100R; R_0603_1608Metric; LCSC Part C22775
R6, R7: 100K; R_0603_1608Metric; LCSC Part C25803
SW1, SW2, SW3, SW4: B3F-1052; SW_PUSH_6mm; LCSC Part C87037
U1: CH32V003F4P6; TSSOP-20_4.4x6.5mm_P0.65mm; LCSC Part C5187096

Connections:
+3V3: C1.1, C2.1, J1.2, J2.2, J5.2, Q1.3 (D), R3.1, U1.9 (VDD)
AUX_5V: C8.1, D5.2 (A), J3.1, J4.1, Q1.1 (G), R6.1
AUX_SENSE: R6.2, R7.1, U1.14 (PC4)
DATA_FWD: J2.3, R2.2
DATA_RET: J1.4, J2.4, R1.2
DO1: D1.1 (DOUT), D2.3 (DIN)
DO2: D2.1 (DOUT), D3.3 (DIN)
DO3: D3.1 (DOUT), D4.3 (DIN)
GND: C1.2, C2.2, C3.2, C4.2, C5.2, C6.2, C7.2, C8.2, D1.2 (VSS), D2.2 (VSS), D3.2 (VSS), D4.2 (VSS), J1.1, J1.5, J2.1, J3.2, J4.2, J5.3, R4.2, R7.2, SW1.2, SW2.2, SW3.2, SW4.2, U1.7 (VSS)
ID: R3.2, R4.1, U1.20 (PD3)
LED_DIN: D1.3 (DIN), R5.2
LED_SPI: R5.1, U1.16 (PC6)
NRST: J5.4, U1.4 (PD7)
PRESENT: J2.5, U1.13 (PC3)
SAT_RX: J1.3, U1.3 (PD6), U1.11 (PC1)
SWIO: J5.1, U1.18 (PD1)
SW_1: SW1.1, U1.5 (PA1)
SW_2: SW2.1, U1.6 (PA2)
SW_3: SW3.1, U1.1 (PD4)
SW_4: SW4.1, U1.8 (PD0)
TX_FWD: R2.1, U1.2 (PD5)
TX_RET: R1.1, U1.10 (PC0)
V_LED: C3.1, C4.1, C5.1, C6.1, C7.1, D1.4 (VDD), D2.4 (VDD), D3.4 (VDD), D4.4 (VDD), D5.1 (K), Q1.2 (S)

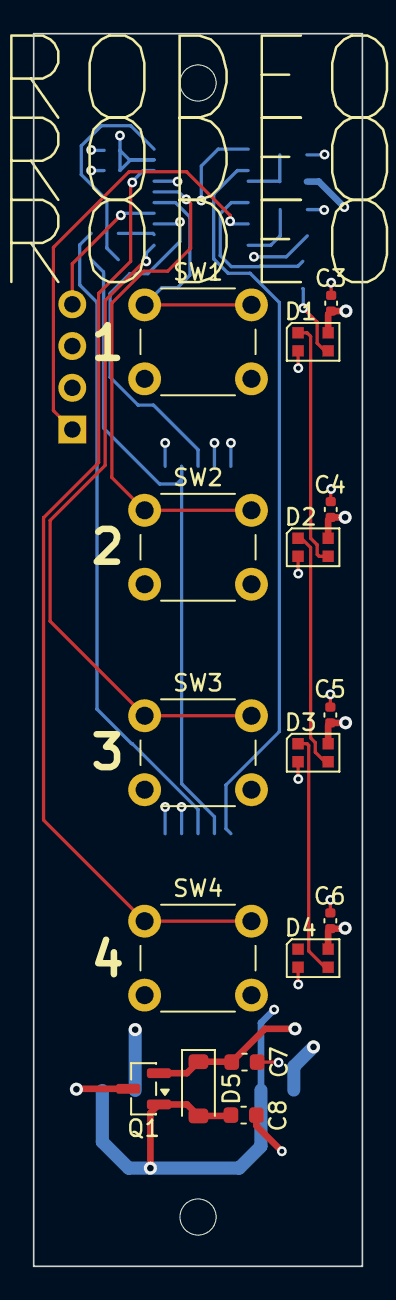
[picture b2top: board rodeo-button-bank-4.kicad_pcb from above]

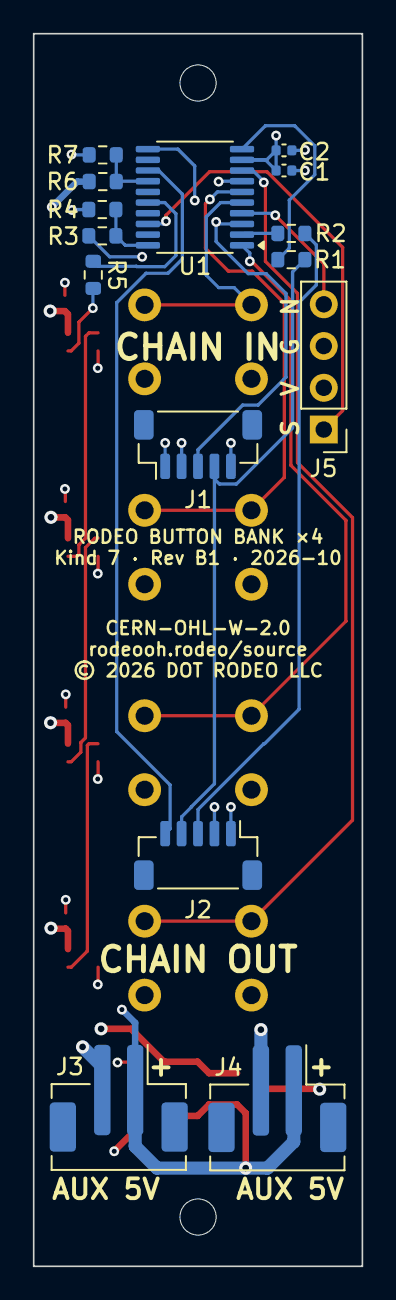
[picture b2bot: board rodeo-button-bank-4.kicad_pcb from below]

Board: 4 copper layers, 20.0 x 75.0 mm, 33 parts (15 on the bottom side), 23 nets.

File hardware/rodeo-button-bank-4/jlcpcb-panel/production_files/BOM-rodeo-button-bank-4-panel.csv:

Comment,Designator,Footprint,LCSC,Quantity
1u,"C1_0,C1_1,C1_2,C1_3",C_0402_1005Metric,C52923,4
100n,"C2_0,C2_1,C2_2,C2_3,C3_0,C3_1,C3_2,C3_3,C4_0,C4_1,C4_2,C4_3,C5_0,C5_1,C5_2,C5_3,C6_0,C6_1,C6_2,C6_3",C_0402_1005Metric,C1525,20
10u,"C7_0,C7_1,C7_2,C7_3,C8_0,C8_1,C8_2,C8_3",C_0603_1608Metric,C19702,8
WS2812B-2020-V6,"D1_0,D1_1,D1_2,D1_3,D2_0,D2_1,D2_2,D2_3,D3_0,D3_1,D3_2,D3_3,D4_0,D4_1,D4_2,D4_3",LED_WS2812B-2020_PLCC4_2.0x2.0mm,C52917434,16
B5819W,"D5_0,D5_1,D5_2,D5_3",D_SOD-123,C8598,4
IN,"J1_0,J1_1,J1_2,J1_3",JST_SH_BM05B-SRSS-TB_1x05-1MP_P1.00mm_Vertical,C160391,4
OUT,"J2_0,J2_1,J2_2,J2_3",JST_SH_BM05B-SRSS-TB_1x05-1MP_P1.00mm_Vertical,C160391,4
AUX IN,"J3_0,J3_1,J3_2,J3_3",JST_PH_B2B-PH-SM4-TB_1x02-1MP_P2.00mm_Vertical,C160352,4
AUX OUT,"J4_0,J4_1,J4_2,J4_3",JST_PH_B2B-PH-SM4-TB_1x02-1MP_P2.00mm_Vertical,C160352,4
AO3401A,"Q1_0,Q1_1,Q1_2,Q1_3",SOT-23,C15127,4
33R,"R1_0,R1_1,R1_2,R1_3,R2_0,R2_1,R2_2,R2_3",R_0603_1608Metric,C23140,8
10K,"R3_0,R3_1,R3_2,R3_3",R_0603_1608Metric,C25804,4
8K66,"R4_0,R4_1,R4_2,R4_3",R_0603_1608Metric,C23114,4
100R,"R5_0,R5_1,R5_2,R5_3",R_0603_1608Metric,C22775,4
100K,"R6_0,R6_1,R6_2,R6_3,R7_0,R7_1,R7_2,R7_3",R_0603_1608Metric,C25803,8
B3F-1052,"SW1_0,SW1_1,SW1_2,SW1_3,SW2_0,SW2_1,SW2_2,SW2_3,SW3_0,SW3_1,SW3_2,SW3_3,SW4_0,SW4_1,SW4_2,SW4_3",SW_PUSH_6mm,C87037,16
CH32V003F4P6,"U1_0,U1_1,U1_2,U1_3",TSSOP-20_4.4x6.5mm_P0.65mm,C5187096,4

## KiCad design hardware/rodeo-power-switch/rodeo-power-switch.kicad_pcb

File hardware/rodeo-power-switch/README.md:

# Rodeo power switch board

A latching push button on the back panel, cabled to the motherboard's power switch
connector (J3). Pressed in, it enables the motherboard's +5 V converter (U5's EN);
out, the synth is off and the battery still charges. Nothing but the switch and the
connector: R12 (10 kΩ, in series from the battery), R13 (47 kΩ to GND) and the
10 nF filter are on the motherboard (see
[`rev-b.md`, "Power"](../rodeo-motherboard/docs/rev-b.md#power)).

Designed 2026-10-16: drawn, laid out, routed and DRC-clean, fab outputs in
`jlcpcb/`. The plunger goes through the 1.6 mm panel's 4.0 × 3.5 mm slot
([`panels/rodeo-power-switch-panel`](../panels/rodeo-power-switch-panel/)) and is
usable bare; a 3D-printed cap is optional (see [Cap](#cap)).

## Connections

**J1, to the motherboard's J3: JST SH 2-pin vertical, BM02B-SRSS-TB (C160388)**,
symbol `Connector_Generic:Conn_01x02`, footprint
`Connector_JST:JST_SH_BM02B-SRSS-TB_1x02-1MP_P1.00mm_Vertical`. The same part as J3,
so a straight SH cable connects them. Polarity doesn't matter to the circuit, but
keep pin 1 to pin 1.

| J1 pin | Net | Goes to | Motherboard J3 |
|---|---|---|---|
| 1 | `SW_A` | SW1 pin 2 | `BATT_VCC` through R12 |
| 2 | `SW_B` | SW1 pin 4 | U5 EN, R13 to GND |

Mounting pads (MP) unconnected: this board has no ground.

**SW1: TK-6580A-1 (C528770)**, Yuandi, right-angle latching push switch, 5.8 × 5.8 mm
body. Symbol `rodeo_power_switch:TK-6580A-1`, footprint
`rodeo_power_switch:SW-TH_TK-6580A-1`, both from LCSC (the footprint's pads checked
against the datasheet). The switch was on the motherboard until 2026-10-08, so the
symbol, footprint and model are copies of the ones in its library, with two changes:
the pins are passive (LCSC had them unspecified), and the plunger outline is on F.Fab
rather than silkscreen, since it lies past the board edge.

| SW1 pins | Released (out) | Latched (in) |
|---|---|---|
| 1–3 | closed | open |
| 2–4 | open | **closed** |
| 5, 6 | extra terminals of 2 and 4 | |

Wire **pins 2 and 4** to J1 and put no-connect flags on 1, 3, 5 and 6; all six pads
are still soldered and hold the switch down. The table is the datasheet's circuit
diagram read with LCSC's pin names (`OFF_A`/`OFF_B` = 1/3, `ON_A` = 2 and 5,
`ON_B` = 4 and 6); XKB's drop-in equivalent (XKB5858-Z-E) draws the same diagram.
**Check it with a meter on a loose switch before ordering**: pins 2–4 should open
and close with each press, and nothing should connect 2 or 4 to 1 or 3 in either
position.

The contacts are silver-plated and carry 50–75 µA when on; that's why R13 is
47 kΩ and not the 1 MΩ it was.

## Board

* **Outline 30 × 20 mm**, I/O edge on top.
* **SW1 at (15, 3.70), rotation 180°**: plunger pointing up, body front flush with
  the I/O edge (the footprint's body front is 3.70 mm from its origin). The plunger
  then reaches 4.8 mm past the edge: 3.3 mm proud of the 1.6 mm panel when
  out, 1.3 mm when latched (2 mm travel).
* **M3 holes at (5, 15) and (25, 15)**: rail row 1, 20 mm apart. Check with
  `tools/kicad/grid_check.py rodeo-power-switch.kicad_pcb --rear top`.
* **J1** between the holes, behind the switch (around (15, 14)), cable leaving
  away from the panel.
* Two layers, two traces. No pour needed.

**Panel opening:** centred on SW1, **18.5 mm above the floor** (board top 15.6 mm,
plunger centre 2.90 mm above the board, measured from the 3D model): a 4.0 ×
3.5 mm slot, r 0.5, clearing the plunger's 3.4 × 2.9 mm shoulder where it passes
the panel. A cap would need the slot widened to its outline plus 0.3 mm a side.

## Panel (production runs)

`panel.json` is a 2 × 2 KiKit panel, 76 × 42 mm: four boards, the second row
turned 180° so every plunger faces out of the panel and the J1 edges face each
other across a 2 mm gap with no tabs. Each board hangs from two 5 mm mouse-bite
tabs, one on each 20 mm side, clear of the holes and J1; 5 mm rails on the left
and right carry the tooling holes and fiducials. `tools/kicad/jlc_fab.py
rodeo-power-switch.kicad_pro --panel` writes it and its JLC files to
`jlcpcb-panel/`. Fifty boards are 13 panels. The prototype run was ordered as
single boards.

## Cap

Optional since the panels went to 1.6 mm, and not drawn yet. If added: printed,
in OpenSCAD alongside the mounting parts (`hardware/mounting/`). It presses onto the plunger, so it is made to the
plunger's measured shape (datasheet and 3D model agree):

* first 2 mm past the body front: 3.4 mm wide × 2.9 mm tall
* from there to the tip (2.8 mm): 2.5 mm wide × 2.0 mm tall, centred 2.90 mm
  above the board

The cap's length sets how far it stands proud of the panel in both positions. Its
socket fits over the 2.5 × 2.0 mm tip only, so it stops on the step and never
bottoms out on the body.

## Library

Parts not in KiCad's own libraries are in `lib/`, registered in this folder's
`sym-lib-table` and `fp-lib-table` as `rodeo_power_switch`:

| File | What |
|---|---|
| `lib/rodeo_power_switch.kicad_sym` | `TK-6580A-1` symbol (LCSC) |
| `lib/rodeo_power_switch.pretty/SW-TH_TK-6580A-1.kicad_mod` | Footprint (LCSC) |
| `lib/rodeo_power_switch.3dshapes/SW-TH_TK-6580A-1.{step,wrl}` | 3D model (LCSC), referenced as `${KIPRJMOD}/lib/rodeo_power_switch.3dshapes/` |

## Silkscreen

Same scheme as the other daughterboards (see
[`silkscreen.md`](../docs/silkscreen.md)):

* **Back block:** `RODEO POWER SWITCH` / `Rev B1 · 2026-10` /
  `CERN-OHL-W-2.0` / `rodeooh.rodeo/source` / `© DOT RODEO LLC`.
* **Front, at J1:** `TO MOTHERBOARD SWITCH` (the motherboard labels J3 `SWITCH`),
  plus a `1` at pin 1.
* **Full-bleed `RODEO`** on the back, as on every board.

## Parts

| Part | Refs | Qty | LCSC |
|---|---|---|---|
| TK-6580A-1 | SW1 | 1 | C528770 |
| BM02B-SRSS-TB | J1 | 1 | C160388 |

Both in stock at JLC on 2026-10-16 (8,185 and 20,080). SW1 is through-hole; JLC
fits it with its through-hole assembly.

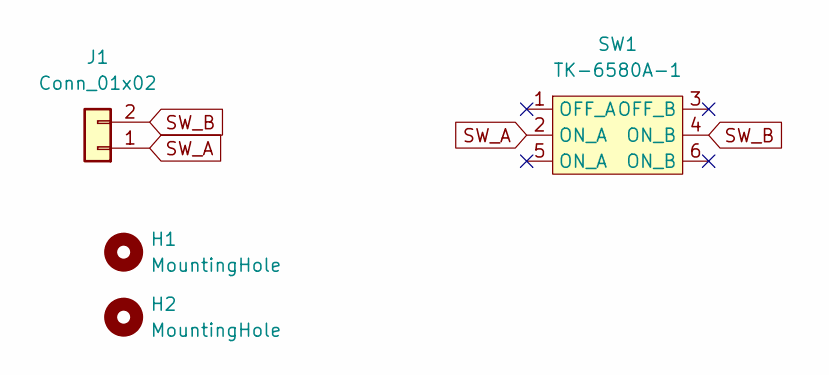
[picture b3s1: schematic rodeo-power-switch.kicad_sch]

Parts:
H1, H2: MountingHole; MountingHole_3.2mm_M3
J1: Conn_01x02; JST_SH_BM02B-SRSS-TB_1x02-1MP_P1.00mm_Vertical; LCSC Part C160388
SW1: TK-6580A-1; SW-TH_TK-6580A-1; MPN TK-6580A-1; LCSC Part C528770

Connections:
SW_A: J1.1, SW1.2 (ON_A)
SW_B: J1.2, SW1.4 (ON_B)

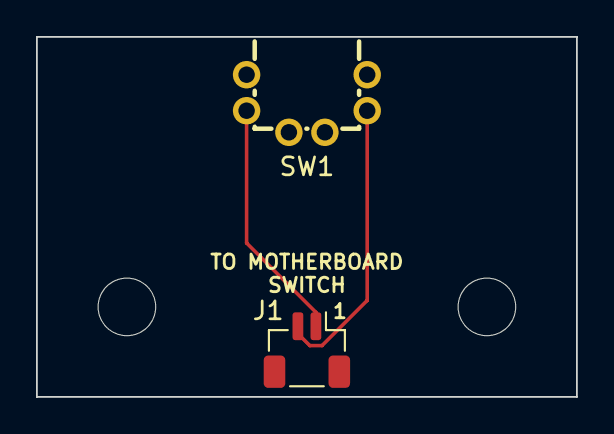
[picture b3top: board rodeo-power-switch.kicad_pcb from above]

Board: 2 copper layers, 30.0 x 20.0 mm, 4 parts (0 on the bottom side), 2 nets.

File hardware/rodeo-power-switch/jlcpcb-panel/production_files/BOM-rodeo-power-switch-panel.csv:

Comment,Designator,Footprint,LCSC,Quantity
Conn_01x02,"J1_0,J1_1,J1_2,J1_3",JST_SH_BM02B-SRSS-TB_1x02-1MP_P1.00mm_Vertical,C160388,4
TK-6580A-1,"SW1_0,SW1_1,SW1_2,SW1_3",SW-TH_TK-6580A-1,C528770,4

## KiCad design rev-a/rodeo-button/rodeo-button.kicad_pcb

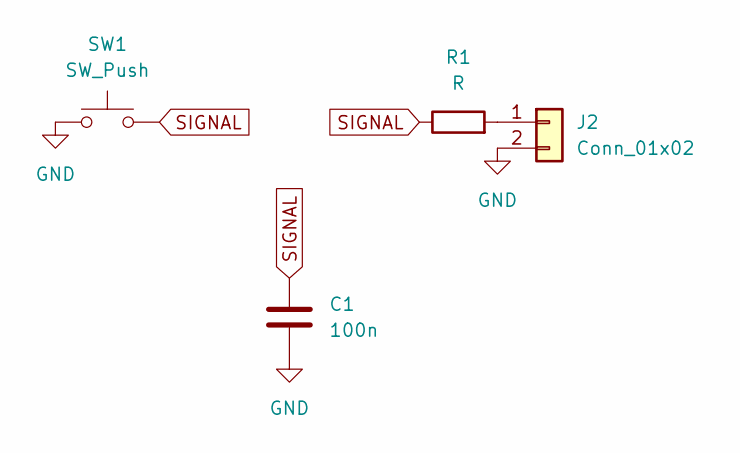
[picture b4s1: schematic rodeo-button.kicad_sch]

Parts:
C1: 100n; C_1206_3216Metric
J2: Conn_01x02; JST_SH_SM02B-SRSS-TB_1x02-1MP_P1.00mm_Horizontal
R1: R; R_1206_3216Metric
SW1: SW_Push; SW_PUSH-12mm

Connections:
GND: C1.2, J2.2, SW1.1
unnamed: J2.1, R1.2
SIGNAL: C1.1, R1.1, SW1.2

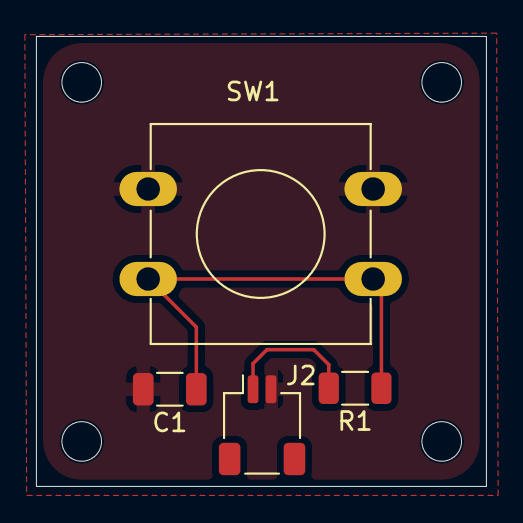
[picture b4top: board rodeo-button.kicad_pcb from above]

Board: 2 copper layers, 25.0 x 25.0 mm, 4 parts (0 on the bottom side), 3 nets.

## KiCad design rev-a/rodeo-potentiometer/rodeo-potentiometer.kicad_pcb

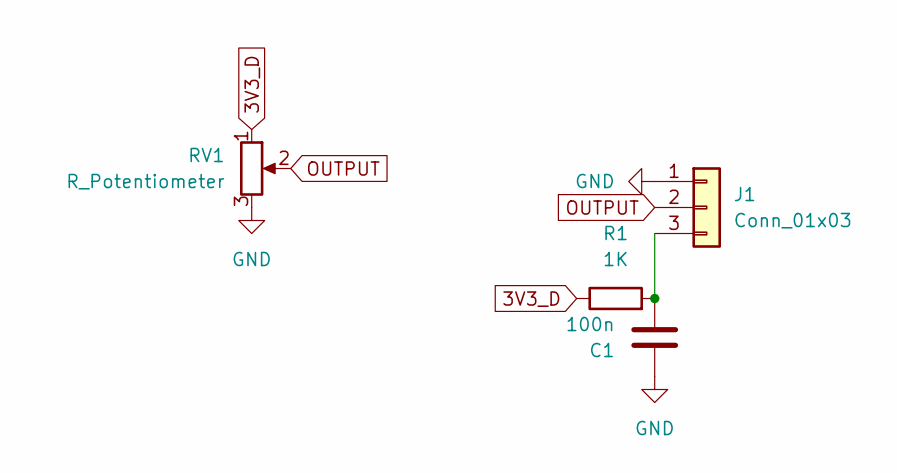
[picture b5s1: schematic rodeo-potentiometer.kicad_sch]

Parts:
C1: 100n; C_0603_1608Metric
J1: Conn_01x03; JST_SH_SM03B-SRSS-TB_1x03-1MP_P1.00mm_Horizontal
R1: 1K; R_0603_1608Metric
RV1: R_Potentiometer; Potentiometer_Alps_RK09K_Single_Vertical

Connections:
3V3_D: R1.1, RV1.1
GND: C1.1, J1.1, RV1.3
unnamed: C1.2, J1.3, R1.2
OUTPUT: J1.2, RV1.2

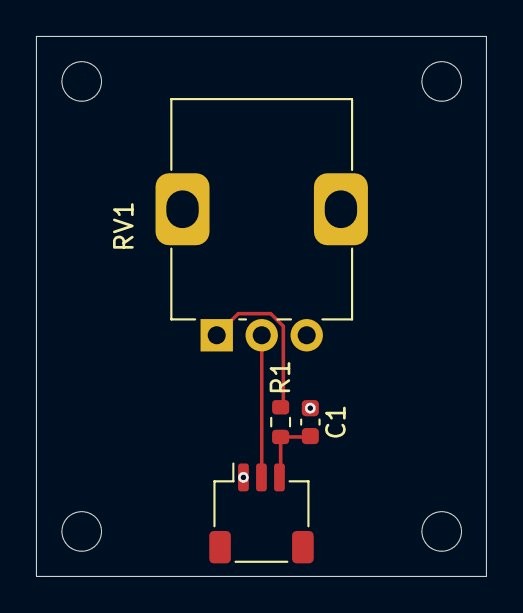
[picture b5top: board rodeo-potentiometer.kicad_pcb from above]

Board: 2 copper layers, 25.0 x 30.0 mm, 4 parts (0 on the bottom side), 4 nets.
